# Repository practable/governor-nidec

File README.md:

# governor-nidec
Governer experiment with nidec motor (spoiler alert - contains friction!)

**WARNING**: This repository contains the early development stages of a remote lab that was never put into full production or testing. You are recommended to use the updated version of the Spinning Disk experiment available at [spinner-amax](https://github.com/practable/spinner-amax).

## PCB
The PCB files are for a version of the PCB intended to work for a number of different hardware setups and used for the Spinner experiment [spinner-nidex](https://github.com/practable/spinner-nidec) and therefore does not represent the best design for the Governor alone. There is currently no PCB design for the Governor experiment specifically.

## UI
This version of the UI is an early production version written with Vue 2. The same UI is used for the digger-nidec, governor-nidec and spinner-nidec experiments. In the App.vue file one line of code will need to be changed depending on which experiment you are running:

`remoteLabVersion: 'spinning_disk', // or 'robot_arm' or 'variable_governor'`

The UI was only ever put into production and tested with the Spinner hardware and development was stopped on the others before they were at a deployable stage. This means that there is no guarantee that the Digger or Governor versions of the UI will work. The UI has been fully upgraded Vue 3 and updated in the [spinner-amax](https://github.com/practable/spinner-amax) repository.

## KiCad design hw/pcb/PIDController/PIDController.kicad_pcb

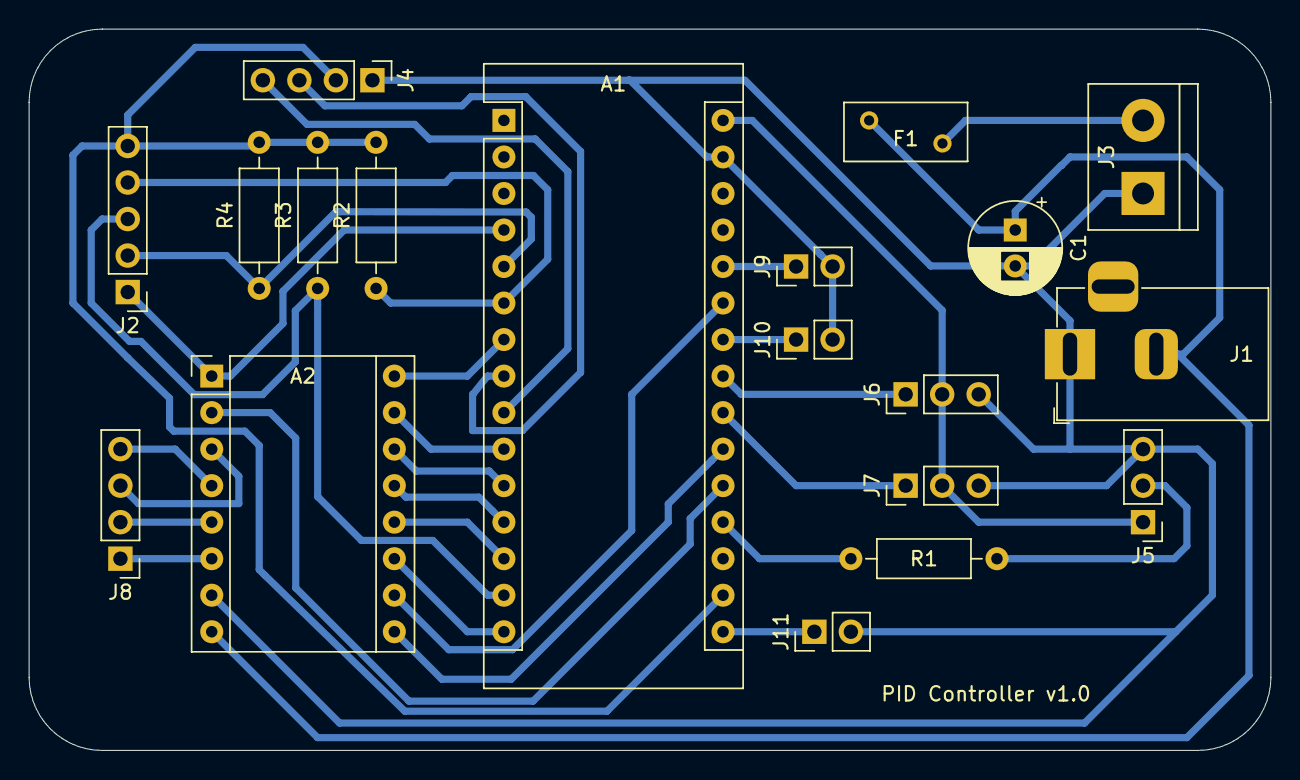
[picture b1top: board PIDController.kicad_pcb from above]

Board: 2 copper layers, 86.4 x 50.2 mm, 19 parts (0 on the bottom side), 30 nets.

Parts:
A1: Arduino_Nano_v3.x; Arduino_Nano
A2: StepperDriver_DRV8825; Pololu_Breakout-16_15.2x20.3mm
C1: 100uF; CP_Radial_D6.3mm_P2.50mm
F1: 2A; Fuse_BelFuse_0ZRE0005FF_L8.3mm_W3.8mm
J1: Barrel_Jack; BarrelJack_Horizontal
J2: Encoder_Conn_01x05; PinHeader_1x05_P2.54mm_Vertical
J3: DC_Motor_Power_OUTPUT; TerminalBlock_bornier-2_P5.08mm
J4: Motor Driver Pins; PinHeader_1x04_P2.54mm_Vertical
J5: Neopixel_Conn_01x03_Male; PinHeader_1x03_P2.54mm_Vertical
J6: Servo_1_Conn; PinHeader_1x03_P2.54mm_Vertical
J7: Servo_2_Conn; PinHeader_1x03_P2.54mm_Vertical
J8: StepperMotor; PinHeader_1x04_P2.54mm_Vertical
J9, J10, J11: Conn_01x02_Female; PinHeader_1x02_P2.54mm_Vertical
R1: 300; R_Axial_DIN0207_L6.3mm_D2.5mm_P10.16mm_Horizontal
R2, R3, R4: 2K7; R_Axial_DIN0207_L6.3mm_D2.5mm_P10.16mm_Horizontal

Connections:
12V: A2.8, C1.1, F1.1, J1.2
DIR: A1.7, A2.16
EN: A1.21, A2.9
FLT: A1.20, A2.2
GND: A1.4, A1.29, A2.1, A2.7, C1.2, J1.1, J2.1, J3.1, J4.1, J5.3, J6.3, J7.3, J9.2, J10.2, J11.2
INDEX: A1.14, J2.3, R3.1
LIMIT1: A1.26, J9.1
LIMIT2: A1.24, J10.1
LIMIT3: A1.16, J11.1
M0: A1.25, A2.10
M1: A1.15, A2.11
M2: A1.13, A2.12
unnamed: A1.5, J2.2, R4.1
unnamed: A1.6, J2.4, R2.1
unnamed: A1.8, J4.3
unnamed: A1.9, J4.4
unnamed: A1.19, R1.1
unnamed: A2.3, J8.3
unnamed: A2.4, J8.4
unnamed: A2.5, J8.2
unnamed: A2.6, J8.1
unnamed: F1.2, J3.2
unnamed: J5.2, R1.2
RST: A1.12, A2.13
SERVO1: A1.23, J6.1
SERVO2: A1.22, J7.1
SLP: A1.11, A2.14
STP: A1.10, A2.15
VCC: A1.17, J2.5, J4.2, R2.2, R3.2, R4.2
VIN: A1.30, J5.1, J6.2, J7.2

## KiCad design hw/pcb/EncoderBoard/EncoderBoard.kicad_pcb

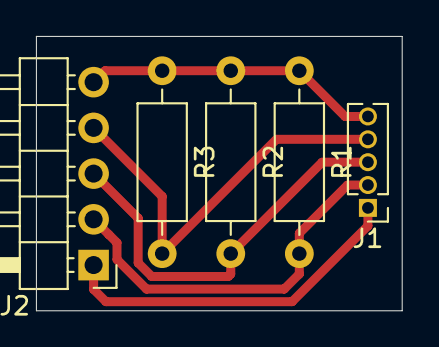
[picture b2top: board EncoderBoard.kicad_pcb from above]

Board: 2 copper layers, 20.3 x 15.2 mm, 5 parts (0 on the bottom side), 5 nets.

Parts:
J1: Conn_01x05_Vert; PinHeader_1x05_P1.27mm_Vertical
J2: Conn_01x05_Horiz; PinHeader_1x05_P2.54mm_Horizontal
R1, R2, R3: 2K7; R_Axial_DIN0207_L6.3mm_D2.5mm_P10.16mm_Horizontal

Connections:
unnamed: J1.1, J2.1
unnamed: J1.2, J2.2, R1.2
unnamed: J1.3, J2.3, R2.2
unnamed: J1.4, J2.4, R3.2
unnamed: J1.5, J2.5, R1.1, R2.1, R3.1

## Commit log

2021-11-18 initial commit of experiment files
2021-11-18 readme update
2021-11-18 hardware docs added
